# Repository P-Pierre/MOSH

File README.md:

**ISS 2018 - 2019             
Mini-Projet MOSH            
Pierre PRIE & Mikita PRAKAPENKA**

Sommaire
========

1. Introduction au projet

	a. Présentation du sujet et des étapes clés
	
	b. Détail du contenue du dossier

2. Montage et développement du projet avec arduino

	a. Communication LoRa 
	
	b. Capteur de gaz connectée et gestion d'interruption
	
	c. Gestion d’énergie
	
	d. Interface Node-RED

3. Réalisation des PCBs pour le projet

	a. Réalisation de étage d’amplification du nanocapteur de gaz
	
	b. Réalisation du SHIELD arduino du projet

1.Introduction au projet
==========================

a. Présentation du sujet et des étapes clés
--------------------------------------------

   Dans le cadre de l’UF “MICRO-CONTRÔLEURS ET OPEN-SOURCE HARDWARE” en 5ème année spécialité “Innovative Smart Systems” nous avons conçus des PCBs visant à récupérer les données d’un nanocapteur de gaz et à les envoyer sur le serveur TTN grâce à la technologie LoRa. Nous avons découpé notre travail en plusieurs étapes : 

* Utiliser la puce RN2483 (LoRa) via l’Arduino UNO pour envoyer des données tests sur le serveur TTN. 

* Câbler et récupérer la réponse du capteur de gaz MQ-5.  

* Câbler un montage comparateur permettant de générer une interruption dès que la concentration en gaz mesuré par le MQ-5 dépasse un certain seuil. Le comparateur est de nature HW.  

* Établir une estimation de la consommation d’énergie du système.  

* Récupérer les données envoyées sur le serveur TTN via Node-RED pour réaliser un affichage graphique des données.  

* Réaliser un SHIELD avec l’ensemble des composants utilisés pour ce projet MOSH (connecteur avec la puce LoRa, avec le capteur de gaz MQ-5, le comparateur LM393, des LED de signalements…).  

* Réaliser une PCB pour l’étage d’amplification du nanocapteur de gaz conçu en salle blanche. Ce PCB est également équipé d’un cavalier et d’un mosfet IRF520 utilisés pour appliquer périodiquement une tension de décharge de 12V au borne du nanocapteur de gaz. 

* Notre SHIELD a finalement été modifié pour pouvoir y connecter la PCB du nanocapteur de gaz et de son étage d'amplification.  

Ce travail va nous permettre d’avoir un système complet qui récupère la réponse du nanocapteur, bien calibré avec le capteur MQ-5 et communiquant via LoRa, TTN et Node-Red. Le système gère la concentration dangereuse du gaz et envoie un message d’alerte, tout en ayant une interface graphique très lisible par l’utilisateur.   

b. Détail du contenue du dossier
--------------------------------

Ce projet comporte 3 dossiers différents :

* Le dossier KiCad regroupe les différents SHIELDS et PCBs réalisés. Les versions finales sont Capteur_Gaz_SB_for_SHield et SHield. Pour la PCB du nanocapteur de gaz et du shield du mini-projet respectivement.

* Le dossier arduino regroupe les codes arduino réalisés et utilisés sur la carte arduino UNO. Ce dossier dispose également d’un fichier.zip avec la librairie utilisé pour l’envoie de données avec LoRa.

* Un dossier IMG avec toutes les captures d'écrans et photos de notre projet.

2.Montage et développement du projet avec arduino	
===================================================

Pour réaliser notre code arduino, nous avons utilisés 2 librairies supplémentaires à celles présentes dans l’environnement arduino :

* La librairie <SoftwareSerial.h> présente dans les dossiers arduino.

* La librairie <rn2xx3.h> disponible à l’adresse : https://github.com/jpmeijers/RN2483-Arduino-Library. 

Cette librairie propose des fonctions d’initialisation et de communication de la puce LoRa avec le serveur TTN.

a. Communication LoRa
-----------------------

Afin d’établir la communication LoRa de la puce RN2483 avec l’antenne et donc le serveur TTN, on doit la connecter à l’Arduino UNO. Le pinout de la puce étant écrit sur son PCB on n’a qu’à connecter les pins correspondantes à l’Arduino ( Tx, Rx, RST, 3v3 et GND). 
Ensuite on suit la démarche du site TheThingsNetwork pour créer une application ainsi qu’un device sur cette application. L’application et le device sont défini par des identifiants : le DEVICE EUI et APPLICATION EUI. Lors de la création du device sur TTN nous avons choisit la méthode d’activation ABP. Le serveur TTN nous génère alors un “devAddr”, un “nwkSKey” et un “appSKey” qui sont utilisés dans notre code arduino pour identifier la puce LoRa et communiquer avec notre instance du serveur TTN.

Le code arduino est divisé en deux grandes parties, une partie void setup() qui  est exécuté une seul fois au démarrage de la carte et une partie void loop() qui s'exécute ensuite jusqu'à ce que la carte ne soit plus alimentée.

La partie void setup() nous permet principalement de tester et d’établir la connexion avec l’antenne LoRa, grâce à la fonction “initialize_radio” et de définir les interruptions. Nous reviendrons sur le fonctionnement des interruptions dans la partie suivante. La fonction “initialize_radio” renvoie différents messages d’initialisation sur le port série de l’ordinateur. Elle établit la connexion avec le serveur TTN grâce aux cléfs “devAddr”, “nwkSKey” et “appSKey”. En cas d'erreur un message spécifique est affiché sur le port série.

Dans la partie void loop(), l’envoie de donnée à la puce LoRa est réalisé avec la commande “myLora.tx(Donnée)”, la fonction découpe et envoie automatiquement les données en paquets de 2 caractères hexadécimale (8bits). 

Ces données sont alors lisibles directement sur TTN dans l’onglet “data” de notre device. Cependant ces données sont affichées sous leurs forme hexadécimale, il est nécessaire de coder un “Payload Formats” pour effectuer un affichage sous forme décimale. 

b. Capteur de gaz connectée et gestion d'interruption
------------------------------------------------------

Le capteur de gaz MQ-5 possède une connexion de type “groove”. C’est un capteur de type analogique, on le connecte donc sur une des pins analogique. Le capteur est également relié à la masse et au 5V. Avant d’envoyer les données mesurées par le capteur de gaz, il faut les transformer en données digital. Pour cela, on divise la valeur lu par 1024 et on multiplie le résultat par 5. Cette formule est donnée dans la datasheet du capteur. Cette “transformation” aurait très bien pu être effectuée plus tard, comme juste avant l’affichage dans l’interface graphique de Node-RED. On note qu’une LED rouge clignote à chaque envoie de donnée via la puce LoRa.

Il est possible de définir des interruptions dans le void setup() du programme Arduino. Les interruptions consistent en une fonction qui sera exécutée à chaque fois que la condition d'interruption est réalisée. Pendant son exécution, le reste du programme est mis en pause. A la fin de son exécution, le programme reprend au début de la Void loop(). 
Une interruption est définie de la manière suivante : “attachInterrupt(1, gestionINT0UP, RISING)”. Ainsi quand un état montant est lu sur la pin 3, l'interruption se déclenche et exécute la fonction gestionINT0UP. Nous avons défini deux interruption différentes, une pour la lecture d’un état montant et une pour un état descendant.
Pour déclencher les interruptions, nous avons utilisé un AOP, le LM393, pour comparer la tension généré par le capteur de gaz MQ-5 et une tension seuil que nous avons défini grâce à un pont diviseur de tension. Ainsi dès que la tension du capteur de gaz MQ-5 dépasse ce seuil, un état haut est généré en sortie de l’AOP. A l’inverse quand la tension du capteur repasse sous le seuil, un état bas est généré. On note qu’une LED rouge s’allume et qu’un message d’alerte est envoyé sur le port série de l’ordinateur quand la tension du capteur de gaz se trouve au dessus du seuil. Dans le cas contraire, la LED s’éteint et un message de retour à l’état normal est envoyé sur le port série.
Utilisation du comparateur nous permet de générer des interruptions sans utiliser une comparaison logiciel qui serait testé à chaque exécution de la boucle.

c.   Gestion de consommation d’énergie
--------------------------------------

On peut estimer la consommation énergétique du système avec un Charger Doctor  qui se branche en série entre le port USB de l'ordinateur et le câble USB de l’Arduino. Il nous affiche la consommation moyenne de 0,280 A avec le capteur de gaz MQ-5 connecté. Or, dès qu’on déconnecte le capteur on tombe à  80mA de consommation. Cela s’explique par le fait que le capteur MQ-5 mesure la concentration des gaz en chauffant une résistance, ce qui n’est pas optimale pour la consommation énergétique. Avec le nanocapteur de gaz en revanche, on pourra espérer avoir une consommation d'énergie beaucoup plus basse. 

d.   Interface Node-RED
-----------------------

Afin de d'afficher les données mesurés par le capteur de gaz et envoyées sur le cloud (TTN), nous avons utilisé l'interface graphique Node-RED, très pratique. 
La première chose à faire, c’est d’installer l’interface sur votre PC. Pour ce faire, on a utilisé un guide de Node-RED pour Windows :  https://nodered.org/docs/platforms/windows. Après avoir installé l’interface on y accède via le terminal (commande “node-red”) et on ouvre l’adresse qu’il nous propose dans un  navigateur Web. Pour pouvoir manipuler les données de TTN, on doit installer une librairie “TheThingsNetwork” dédiée. 
A partir de maintenant on peut assembler l’interface, qui nous permettra d’afficher proprement les données du capteur. Tout d’abord on configure la partie “device” avec les identifiants de l’application TTN dédiée. Si tout a été bien saisi, on verra un voyant vert et le message “connected” à côté du “device”. Ensuite on va rajouter une fonction “get payload” à la suite du “device” qui va nous permettre de récupérer le message utile : msg = {value: msg.payload['payload']};return msg. Puis on connecte un afficheur “graphique en fonction du temps” et une "jauge"  à la suite de la fonction, pour pouvoir enfin afficher les données. En cliquant sur “Deploy” et puis sur le “dashboard” on affiche les données en temps réel dans un nouvel onglet. 
Sur les images suivantes vous voyez la réponse du capteur de gaz: normale au début, puis “rouge” à cause d’une concentration importante du gaz dangereux, et qui repasse en normale après. Vous y trouverez aussi notre interface Node-RED.

3.Réalisation des PCBs pour le projet
======================================

Pour réaliser l’ensemble de nos PCBs, nous avons utilisé le logiciel Open-Source Kicad qui permet de réaliser un circuit électrique et son routage. On commence par réaliser le circuit électronique, en définissant si nécessaire de nouvelles librairies pour les composants inexistant. On assigne ensuite une empreinte à chacun des composants avant de pouvoir réaliser le routage. 

a. Réalisation de étage d’amplification du nanocapteur de gaz
-------------------------------------------------------------

L’objectif était ici de réaliser le routage de l’étage d’amplification du nanocapteur de gaz, que nous avions testé et défini en TP. Nous avons également rajouté un mosfet IRF520 contrôlable par une pin de la carte arduino qui permettra d’appliquer une tension de décharge de 12V au borne du nanocapteur de gaz périodiquement. Un cavalier à été ajouté pour connecter la tension de décharge de 12V.
La PCB a été conçue pour venir se connecter sur le SHIELD arduino de notre projet MOSH.

b. Réalisation du SHIELD arduino du projet
------------------------------------------

L’ensemble de notre montage utilisé durant le mini-projet  a été routé sur un SHIELD pour Arduino UNO. Ce SHIELD comprend l’ensemble des LEDs, résistances, condensateurs, l’AOP, le connecteur du capteur de gaz MQ-5 ainsi que des connecteurs pour la puce LoRa et l’étage d’amplification du nanocapteur de gaz. L’ensemble de ces fichiers sont disponibles dans le dossier KiCad.

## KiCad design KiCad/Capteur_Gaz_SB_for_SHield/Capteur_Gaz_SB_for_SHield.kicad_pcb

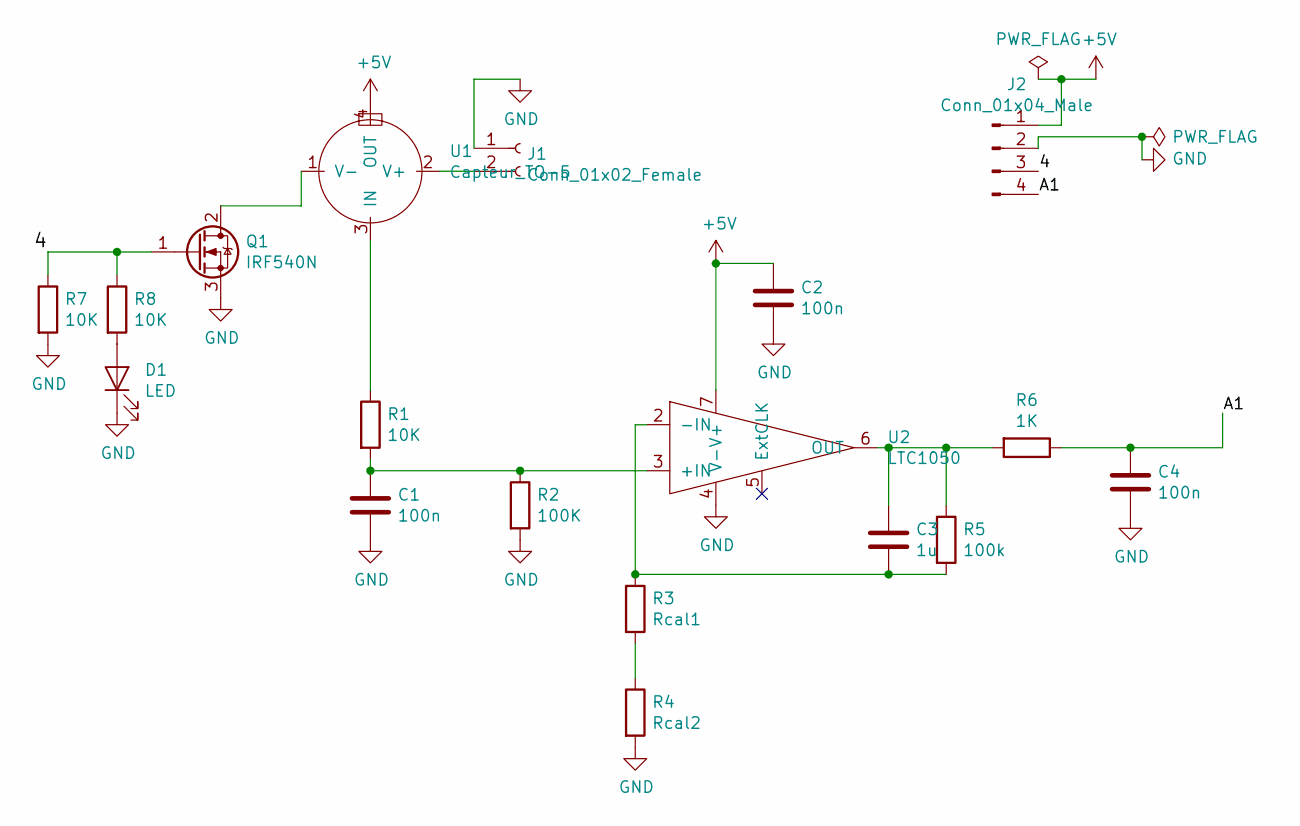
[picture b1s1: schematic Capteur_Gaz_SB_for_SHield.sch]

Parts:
C1, C2, C4: 100n; C_Rect_L7.0mm_W2.5mm_P5.00mm
C3: 1u; C_Rect_L7.0mm_W2.5mm_P5.00mm
D1: LED; LED_D3.0mm_FlatTop
J1: Conn_01x02_Female; PhoenixContact_MSTBVA_2,5_2-G-5,08_1x02_P5.08mm_Vertical
J2: Conn_01x04_Male; PinSocket_1x04_P2.54mm_Vertical
Q1: IRF540N; TO-220-3_Vertical
R1, R7, R8: 10K; R_Axial_DIN0204_L3.6mm_D1.6mm_P7.62mm_Horizontal
R2: 100K; R_Axial_DIN0204_L3.6mm_D1.6mm_P7.62mm_Horizontal
R3: Rcal1; R_Axial_DIN0204_L3.6mm_D1.6mm_P7.62mm_Horizontal
R4: Rcal2; R_Axial_DIN0204_L3.6mm_D1.6mm_P7.62mm_Horizontal
R5: 100k; R_Axial_DIN0204_L3.6mm_D1.6mm_P7.62mm_Horizontal
R6: 1K; R_Axial_DIN0204_L3.6mm_D1.6mm_P7.62mm_Horizontal
U1: Capteur_TO-5; TO-5-4
U2: LTC1050; DIP-8_W7.62mm_Socket_LongPads

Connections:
+5V: C2.1, J2.1, U1.4 (OUT), U2.7 (V+)
/4: J2.3, Q1.1 (G), R7.1, R8.1
/A1: C4.1, J2.4, R6.1
GND: C1.2, C2.2, C4.2, D1.1 (K), J1.1, J2.2, Q1.3 (S), R2.2, R4.2, R7.2, U2.4 (V-)
unnamed: C1.1, R1.2, R2.1, U2.3 (+IN)
unnamed: C3.1, R5.1, R6.2, U2.6 (OUT)
unnamed: C3.2, R3.1, R5.2, U2.2 (-IN)
unnamed: D1.2 (A), R8.2
unnamed: J1.2, U1.2 (V+)
unnamed: Q1.2 (D), U1.1 (V-)
unnamed: R1.1, U1.3 (IN)
unnamed: R3.2, R4.1

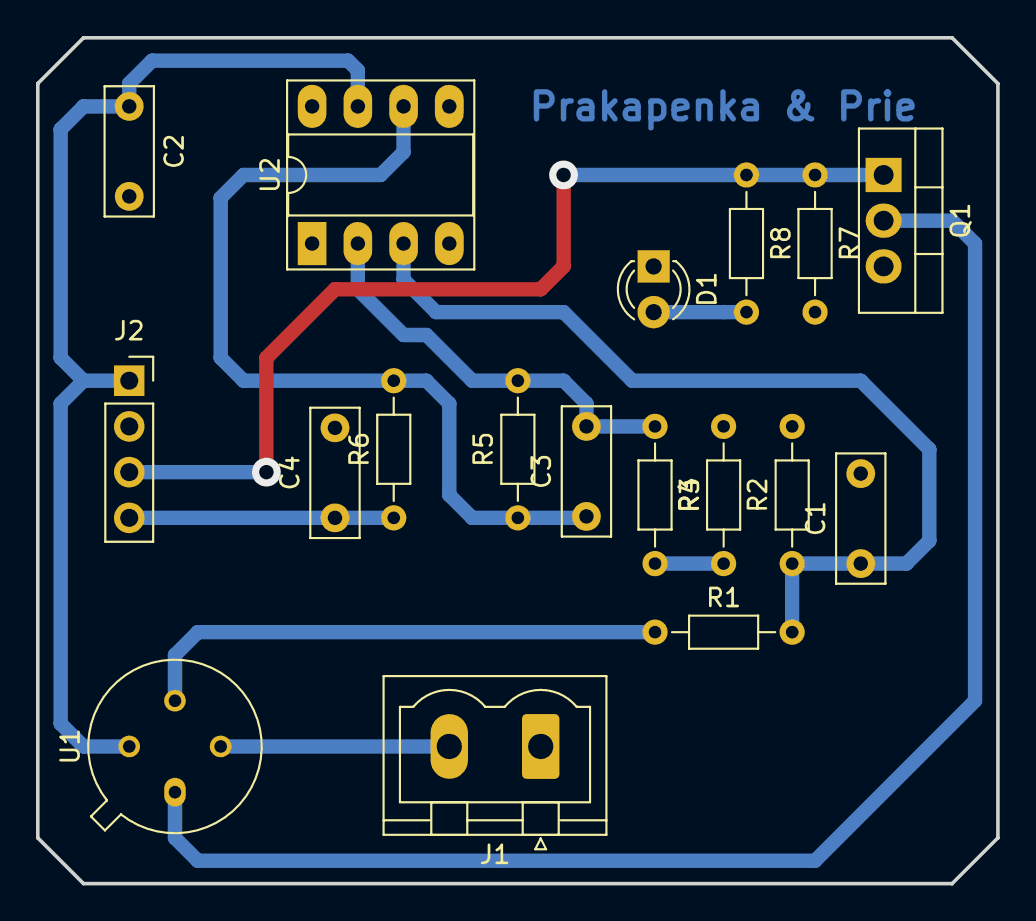
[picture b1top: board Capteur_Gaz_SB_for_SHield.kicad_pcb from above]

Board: 2 copper layers, 53.3 x 47.0 mm, 18 parts (0 on the bottom side), 12 nets.

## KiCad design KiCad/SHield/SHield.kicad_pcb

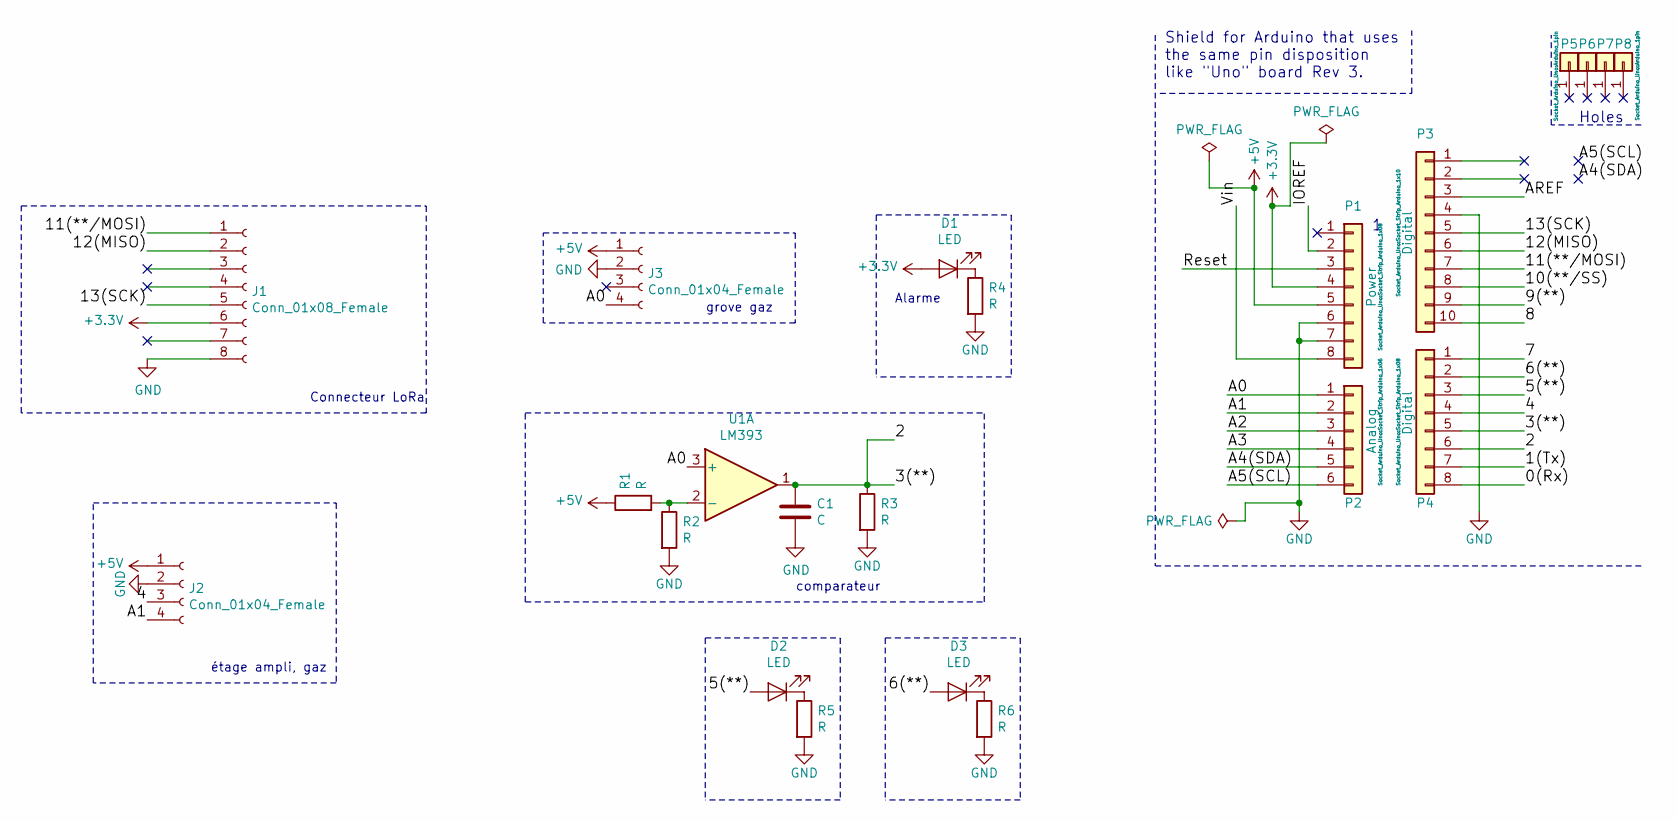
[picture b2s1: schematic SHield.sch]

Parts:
C1: C; CP_Radial_D8.0mm_P5.00mm
D1, D2, D3: LED; LED_D3.0mm_FlatTop
J1: Conn_01x08_Female; PinSocket_1x08_P2.54mm_Vertical
J2: Conn_01x04_Female; PinSocket_1x04_P2.54mm_Vertical
J3: Conn_01x04_Female; NS-Tech_Grove_1x04_P2mm_Vertical
P1: Power; Socket_Strip_Arduino_1x08
P2: Analog; Socket_Strip_Arduino_1x06
P3: Digital; Socket_Strip_Arduino_1x10
P4: Digital; Socket_Strip_Arduino_1x08
P5, P6, P7, P8: CONN_01X01; Arduino_1pin
R1, R2, R3, R4, R5, R6: R; R_Axial_DIN0204_L3.6mm_D1.6mm_P5.08mm_Horizontal
U1: LM393; DIP-8_W7.62mm_LongPads

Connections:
+3V3: D1.2 (A), J1.6, P1.4
+5V: J2.1, J3.1, P1.5, R1.1
/0(Rx): P4.8
/1(Tx): P4.7
/2: C1.1, P4.5, P4.6, R3.1, U1.1
/4: J2.3, P4.4
/5(**): D2.2 (A), P4.3
/6(**): D3.2 (A), P4.2
/7: P4.1
/8: P3.10
/9(**): P3.9
/10(**/SS): P3.8
/11(**/MOSI): J1.1, P3.7
/12(MISO): J1.2, P3.6
/13(SCK): J1.5, P3.5
/A0: J3.4, P2.1, U1.3 (+)
/A1: J2.4, P2.2
/A2: P2.3
/A3: P2.4
/A4(SDA): P2.5
/A5(SCL): P2.6
/AREF: P3.3
/IOREF: P1.2
/Reset: P1.3
/Vin: P1.8
GND: C1.2, J1.8, J2.2, J3.2, P1.6, P1.7, P3.4, R2.2, R3.2, R4.2, R5.2, R6.2
unnamed: D1.1 (K), R4.1
unnamed: D2.1 (K), R5.1
unnamed: D3.1 (K), R6.1
unnamed: R1.2, R2.1, U1.2 (-)

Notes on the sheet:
Holes
Shield for Arduino that uses the same pin disposition like "Uno" board Rev 3.
Connecteur LoRa
étage ampli, gaz
grove gaz
comparateur
Alarme

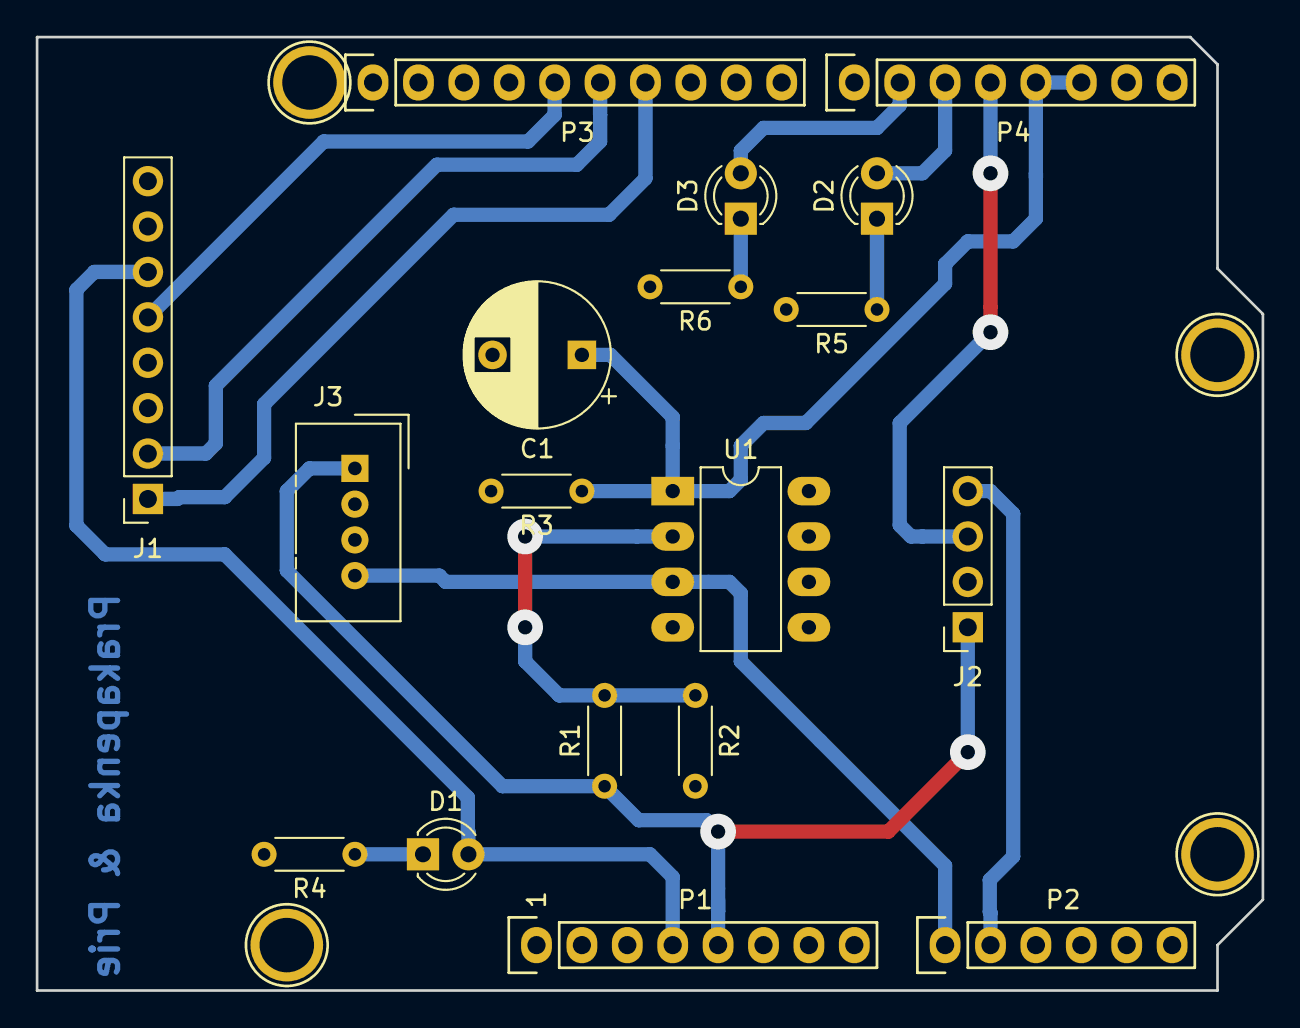
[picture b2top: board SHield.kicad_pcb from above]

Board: 2 copper layers, 68.6 x 53.3 mm, 22 parts (0 on the bottom side), 16 nets.

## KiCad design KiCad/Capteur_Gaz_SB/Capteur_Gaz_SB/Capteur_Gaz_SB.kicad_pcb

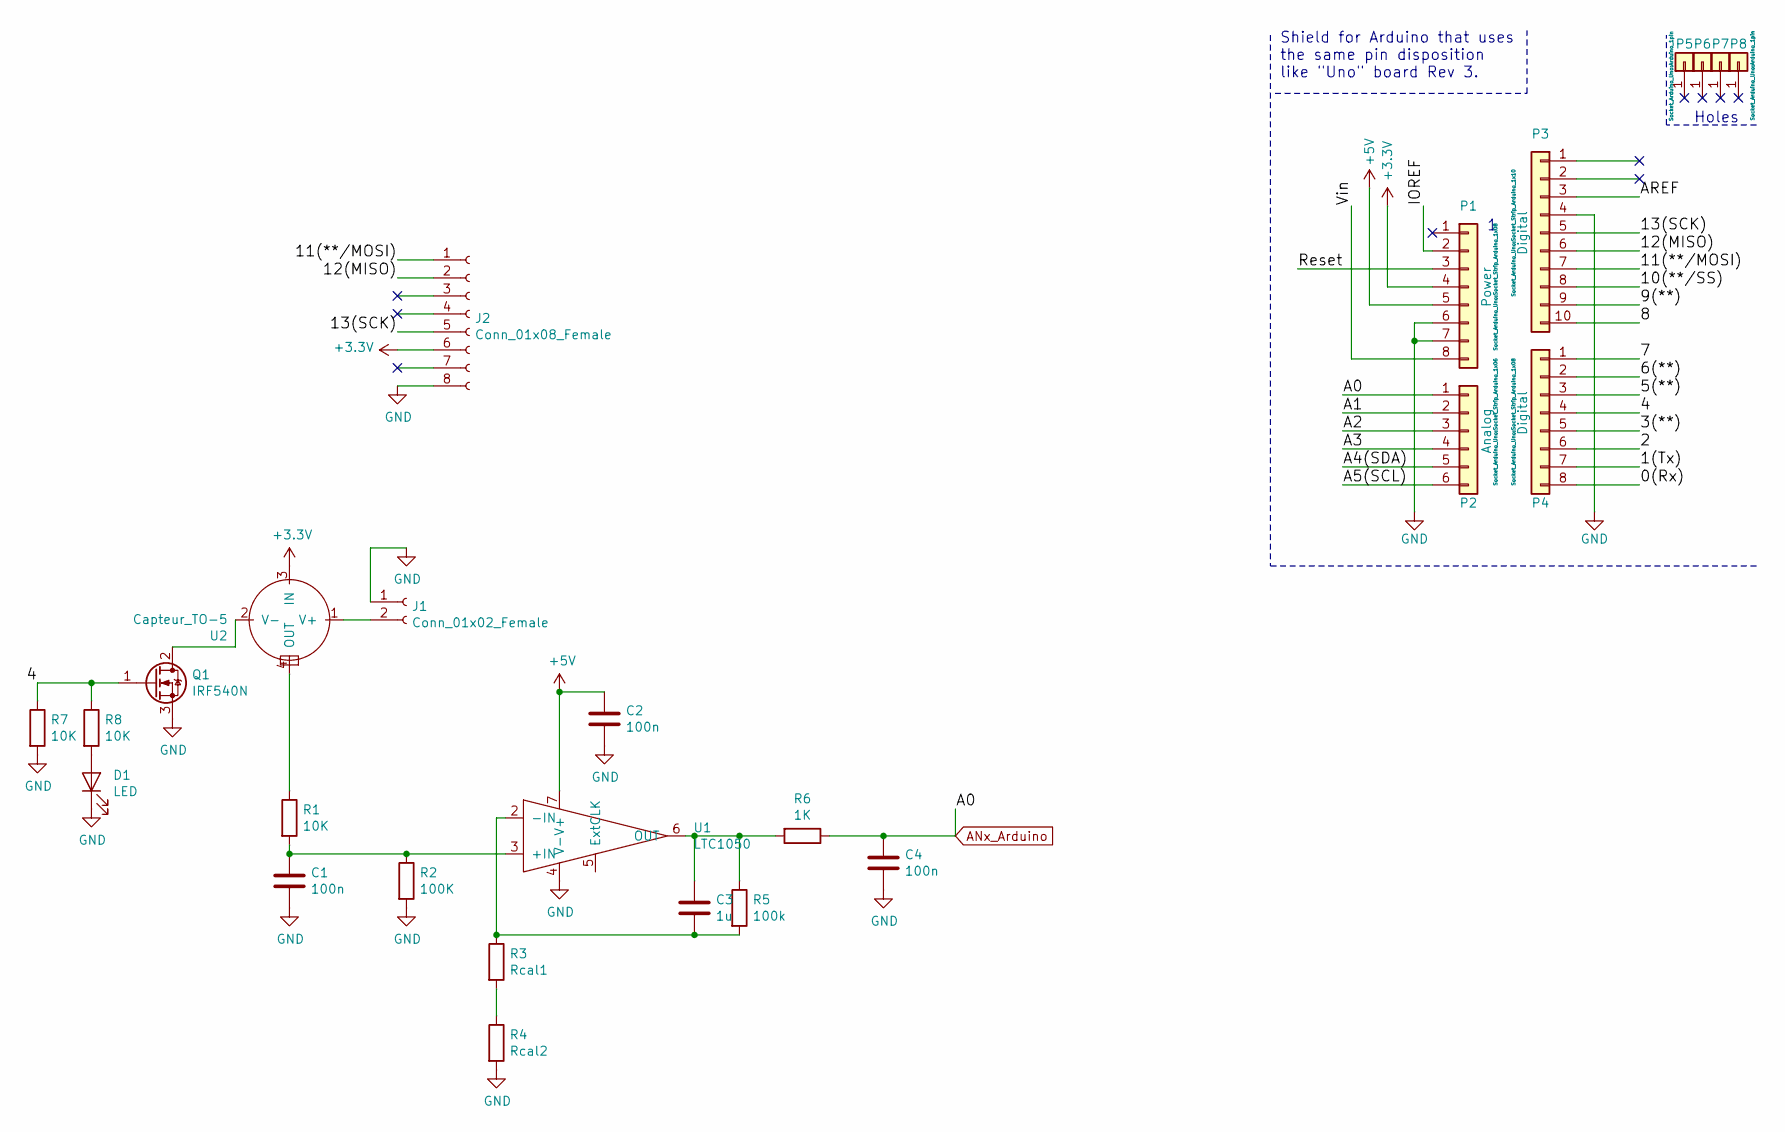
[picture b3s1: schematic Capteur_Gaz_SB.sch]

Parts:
C1, C2, C4: 100n; C_Rect_L7.0mm_W2.5mm_P5.00mm
C3: 1u; C_Rect_L7.0mm_W2.5mm_P5.00mm
D1: LED; LED_D3.0mm_FlatTop
J1: Conn_01x02_Female; PhoenixContact_MSTBVA_2,5_2-G-5,08_1x02_P5.08mm_Vertical
J2: Conn_01x08_Female; PinSocket_1x08_P2.54mm_Vertical
P1: Power; Socket_Strip_Arduino_1x08
P2: Analog; Socket_Strip_Arduino_1x06
P3: Digital; Socket_Strip_Arduino_1x10
P4: Digital; Socket_Strip_Arduino_1x08
P5, P6, P7, P8: CONN_01X01; Arduino_1pin
Q1: IRF540N; TO-220-3_Vertical
R1, R7, R8: 10K; R_Axial_DIN0204_L3.6mm_D1.6mm_P7.62mm_Horizontal
R2: 100K; R_Axial_DIN0204_L3.6mm_D1.6mm_P7.62mm_Horizontal
R3: Rcal1; R_Axial_DIN0204_L3.6mm_D1.6mm_P7.62mm_Horizontal
R4: Rcal2; R_Axial_DIN0204_L3.6mm_D1.6mm_P7.62mm_Horizontal
R5: 100k; R_Axial_DIN0204_L3.6mm_D1.6mm_P7.62mm_Horizontal
R6: 1K; R_Axial_DIN0204_L3.6mm_D1.6mm_P7.62mm_Horizontal
U1: LTC1050; DIP-8_W7.62mm_Socket_LongPads
U2: Capteur_TO-5; TO-5-4

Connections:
+3V3: J2.6, P1.4, U2.3 (IN)
+5V: C2.1, P1.5, U1.7 (V+)
/0(Rx): P4.8
/1(Tx): P4.7
/2: P4.6
/3(**): P4.5
/4: P4.4, Q1.1 (G), R7.1, R8.1
/5(**): P4.3
/6(**): P4.2
/7: P4.1
/8: P3.10
/9(**): P3.9
/10(**/SS): P3.8
/11(**/MOSI): J2.1, P3.7
/12(MISO): J2.2, P3.6
/13(SCK): J2.5, P3.5
/A1: P2.2
/A2: P2.3
/A3: P2.4
/A4(SDA): P2.5
/A5(SCL): P2.6
/AREF: P3.3
/IOREF: P1.2
/Reset: P1.3
/Vin: P1.8
ANx_Arduino: C4.1, P2.1, R6.1
GND: C1.2, C2.2, C4.2, D1.1 (K), J1.1, J2.8, P1.6, P1.7, P3.4, Q1.3 (S), R2.2, R4.2, R7.2, U1.4 (V-)
unnamed: C1.1, R1.2, R2.1, U1.3 (+IN)
unnamed: C3.1, R5.1, R6.2, U1.6 (OUT)
unnamed: C3.2, R3.1, R5.2, U1.2 (-IN)
unnamed: D1.2 (A), R8.2
unnamed: J1.2, U2.1 (V+)
unnamed: Q1.2 (D), U2.2 (V-)
unnamed: R1.1, U2.4 (OUT)
unnamed: R3.2, R4.1

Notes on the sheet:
Holes
Shield for Arduino that uses the same pin disposition like "Uno" board Rev 3.

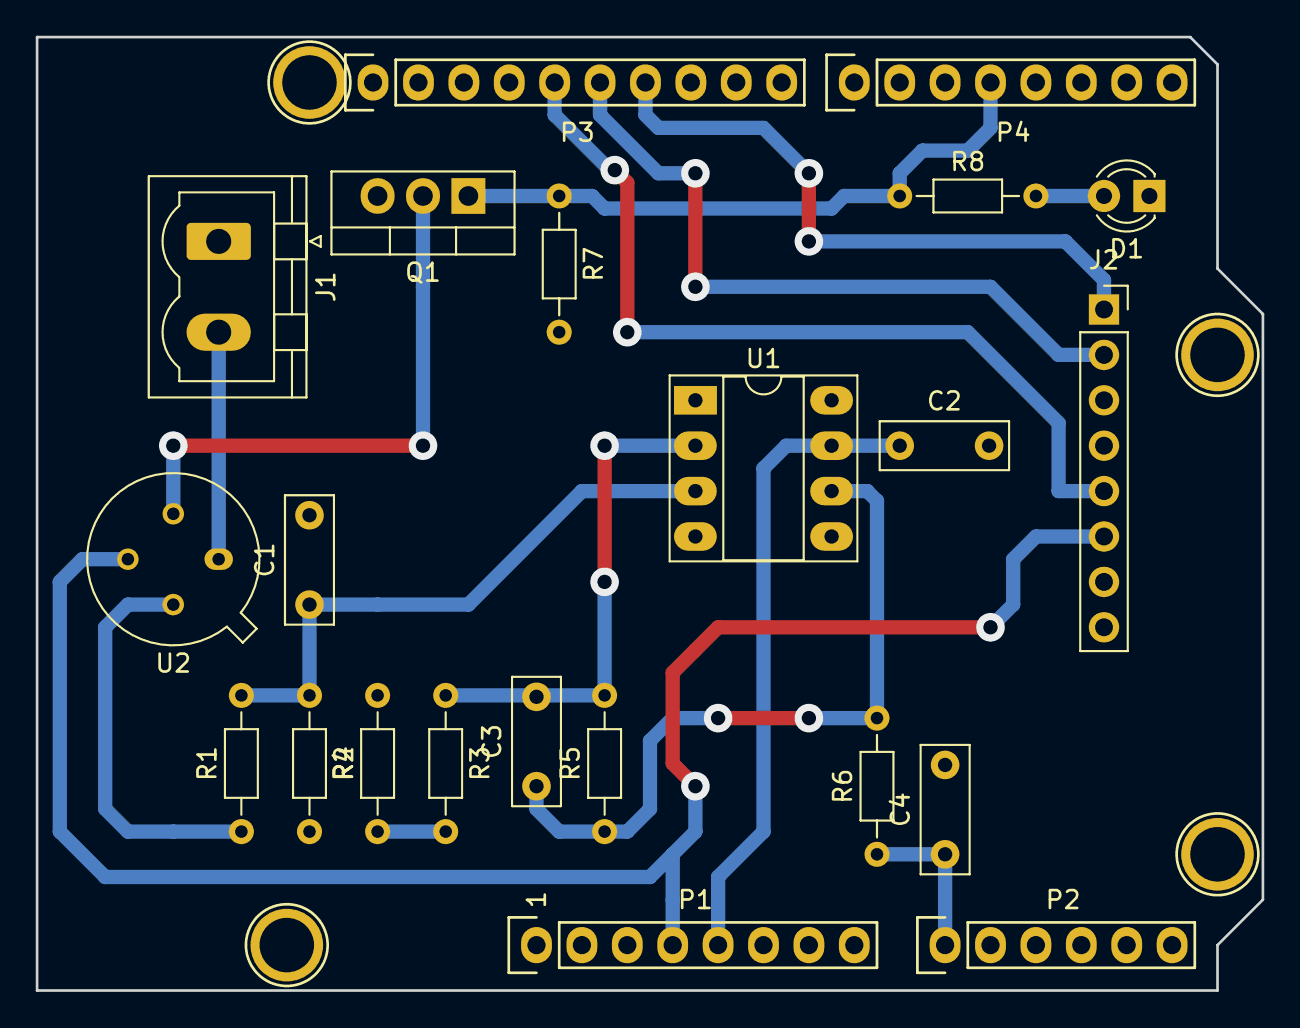
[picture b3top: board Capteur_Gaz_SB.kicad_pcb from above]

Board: 2 copper layers, 68.6 x 53.3 mm, 26 parts (0 on the bottom side), 16 nets.

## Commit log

2018-10-29 ajout du KiCad
2018-10-29 ajout shield capteur gaz SB
2018-10-29 ajout pour de bon
2018-10-29 fin shield SB
2018-11-06 modification et ajout carte pour capteur en salle blanche
2018-11-07 Modifications deu shield, ajout de deux LED
2018-11-07 ajout des fichiers arduino et lib utilisé. Ajout d'un dossier IMG
2018-11-07 ajout d'images
2018-11-27 Découpage des images
2018-11-28 Ajout du text sur les pcbs
2018-11-28 Version physique actuel de Kicad
